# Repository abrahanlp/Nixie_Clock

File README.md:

# Nixie_Clock
 Nixie display clock custom Arduino based.

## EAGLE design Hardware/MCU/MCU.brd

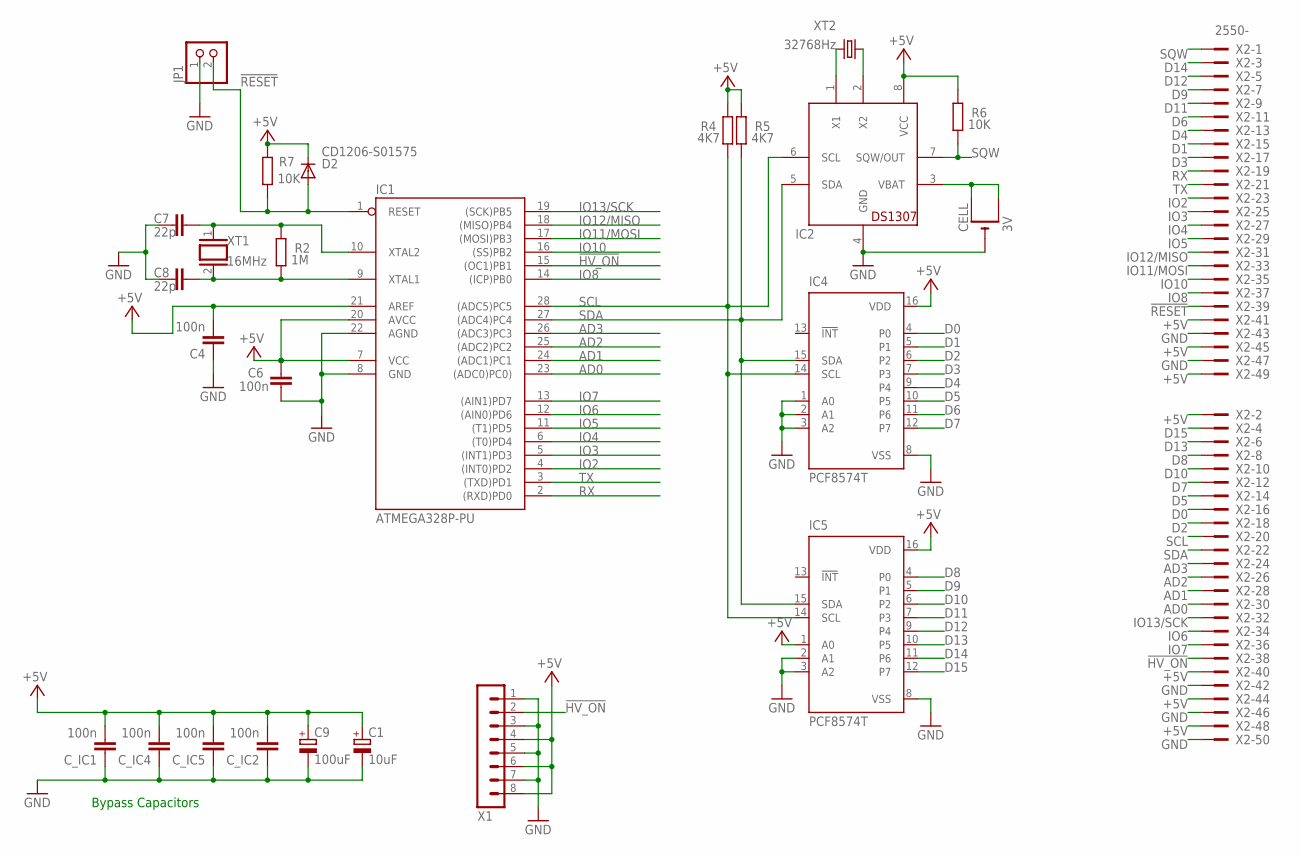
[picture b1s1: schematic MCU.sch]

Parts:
C1: 10uF; 085CS_1AR
C4, C6: 100n; C1206
C7, C8: 22p; C1206
C9: 100uF; E5-10,5
CELL: 3V; CR2032-THRU
C_IC1, C_IC2, C_IC4, C_IC5: 100n; C1206
D2: CD1206-S01575; DO41-10
IC1: ATMEGA328P-PU; DIL28-3
IC2: DS1307; DIL08
IC4, IC5: PCF8574T; SO16W
JP1: PINHD-1X2; 1X02
R2: 1M; M1206
R4, R5: 4K7; M1206
R6, R7: 10K; M1206
X1: MA08-1W
X2: 2550-; PAK100/2500-50
XT1: 16MHz; QS
XT2: 32768Hz; TC26H

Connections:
!HV_ON: IC1.15 ((OC1)PB1), X1.2, X2.38
!RESET: D2.A, IC1.1 (RESET), JP1.2, R7.1, X2.39
+5V: C1.+, C4.2, C6.2, C9.+, C_IC1.2, C_IC2.2, C_IC4.2, C_IC5.2, D2.C, IC1.7 (VCC), IC1.20 (AVCC), IC1.21 (AREF), IC2.8 (VCC), IC4.16 (VDD), IC5.1 (A0), IC5.16 (VDD), R4.2, R5.2, R6.2, R7.2, X1.4, X1.6, X1.8, X2.2, X2.40, X2.41, X2.44, X2.45, X2.48, X2.49
AD0: IC1.23 ((ADC0)PC0)), X2.30
AD1: IC1.24 ((ADC1)PC1), X2.28
AD2: IC1.25 ((ADC2)PC2), X2.26
AD3: IC1.26 ((ADC3)PC3), X2.24
D0: IC4.4 (P0), X2.16
D1: IC4.5 (P1), X2.15
D2: IC4.6 (P2), X2.18
D3: IC4.7 (P3), X2.17
D4: IC4.9 (P4), X2.13
D5: IC4.10 (P5), X2.14
D6: IC4.11 (P6), X2.11
D7: IC4.12 (P7), X2.12
D8: IC5.4 (P0), X2.8
D9: IC5.5 (P1), X2.7
D10: IC5.6 (P2), X2.10
D11: IC5.7 (P3), X2.9
D12: IC5.9 (P4), X2.5
D13: IC5.10 (P5), X2.6
D14: IC5.11 (P6), X2.3
D15: IC5.12 (P7), X2.4
GND: C1.-, C4.1, C6.1, C7.1, C8.1, C9.-, CELL.-, C_IC1.1, C_IC2.1, C_IC4.1, C_IC5.1, IC1.8 (GND), IC1.22 (AGND), IC2.4 (GND), IC4.1 (A0), IC4.2 (A1), IC4.3 (A2), IC4.8 (VSS), IC5.2 (A1), IC5.3 (A2), IC5.8 (VSS), JP1.1, X1.1, X1.3, X1.5, X1.7, X2.42, X2.43, X2.46, X2.47, X2.50
IO2: IC1.4 ((INT0)PD2), X2.23
IO3: IC1.5 ((INT1)PD3), X2.25
IO4: IC1.6 ((T0)PD4), X2.27
IO5: IC1.11 ((T1)PD5), X2.29
IO6: IC1.12 ((AIN0)PD6), X2.34
IO7: IC1.13 ((AIN1)PD7), X2.36
IO8: IC1.14 ((ICP)PB0), X2.37
IO10: IC1.16 ((SS)PB2), X2.35
IO11/MOSI: IC1.17 ((MOSI)PB3), X2.33
IO12/MISO: IC1.18 ((MISO)PB4), X2.31
IO13/SCK: IC1.19 ((SCK)PB5), X2.32
RX: IC1.2 ((RXD)PD0), X2.19
SCL: IC1.28 ((ADC5)PC5), IC2.6 (SCL), IC4.14 (SCL), IC5.14 (SCL), R4.1, X2.20
SDA: IC1.27 ((ADC4)PC4), IC2.5 (SDA), IC4.15 (SDA), IC5.15 (SDA), R5.1, X2.22
SQW: IC2.7 (SQW/OUT), R6.1, X2.1
TX: IC1.3 ((TXD)PD1), X2.21
VBAT: CELL.+1 (+), CELL.+2 (+1), IC2.3 (VBAT)
X1_RTC: IC2.1 (X1), XT2.2
X2_RTC: IC2.2 (X2), XT2.1
XTAL1: C8.2, IC1.9 (XTAL1), R2.1, XT1.2
XTAL2: C7.2, IC1.10 (XTAL2), R2.2, XT1.1

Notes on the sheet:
Bypass Capacitors

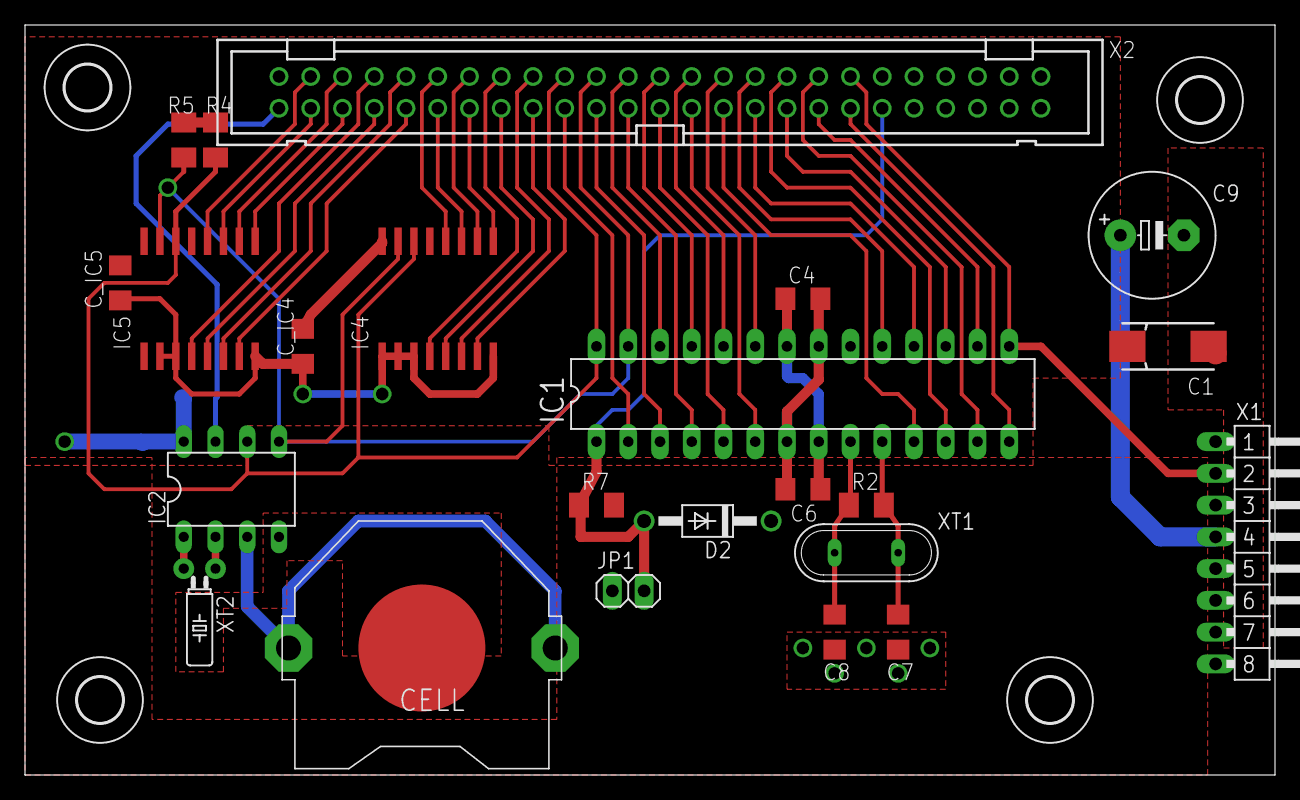
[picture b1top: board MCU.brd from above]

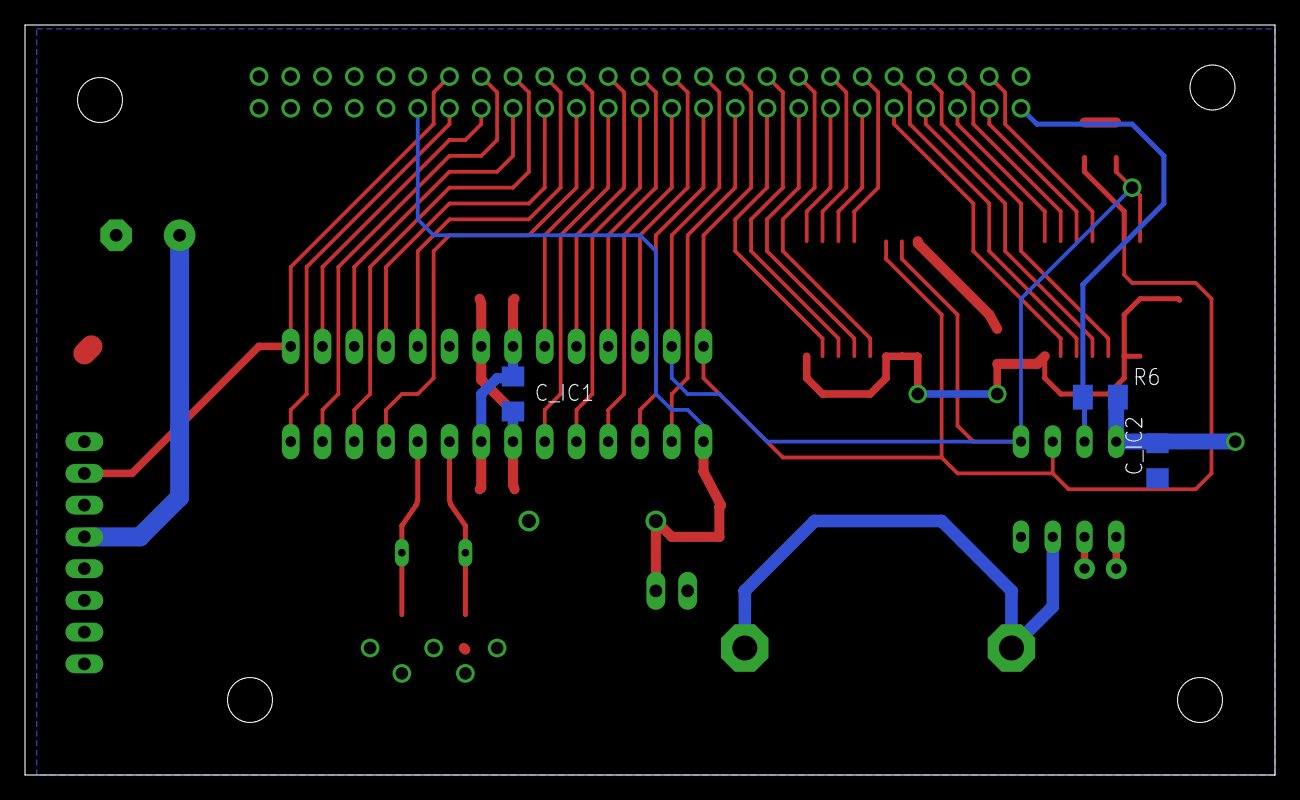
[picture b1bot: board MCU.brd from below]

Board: 2 copper layers, 100.0 x 60.0 mm, 30 parts (3 on the bottom side), 45 nets.

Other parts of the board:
U$1, U$2, U$3, U$4: 3,6

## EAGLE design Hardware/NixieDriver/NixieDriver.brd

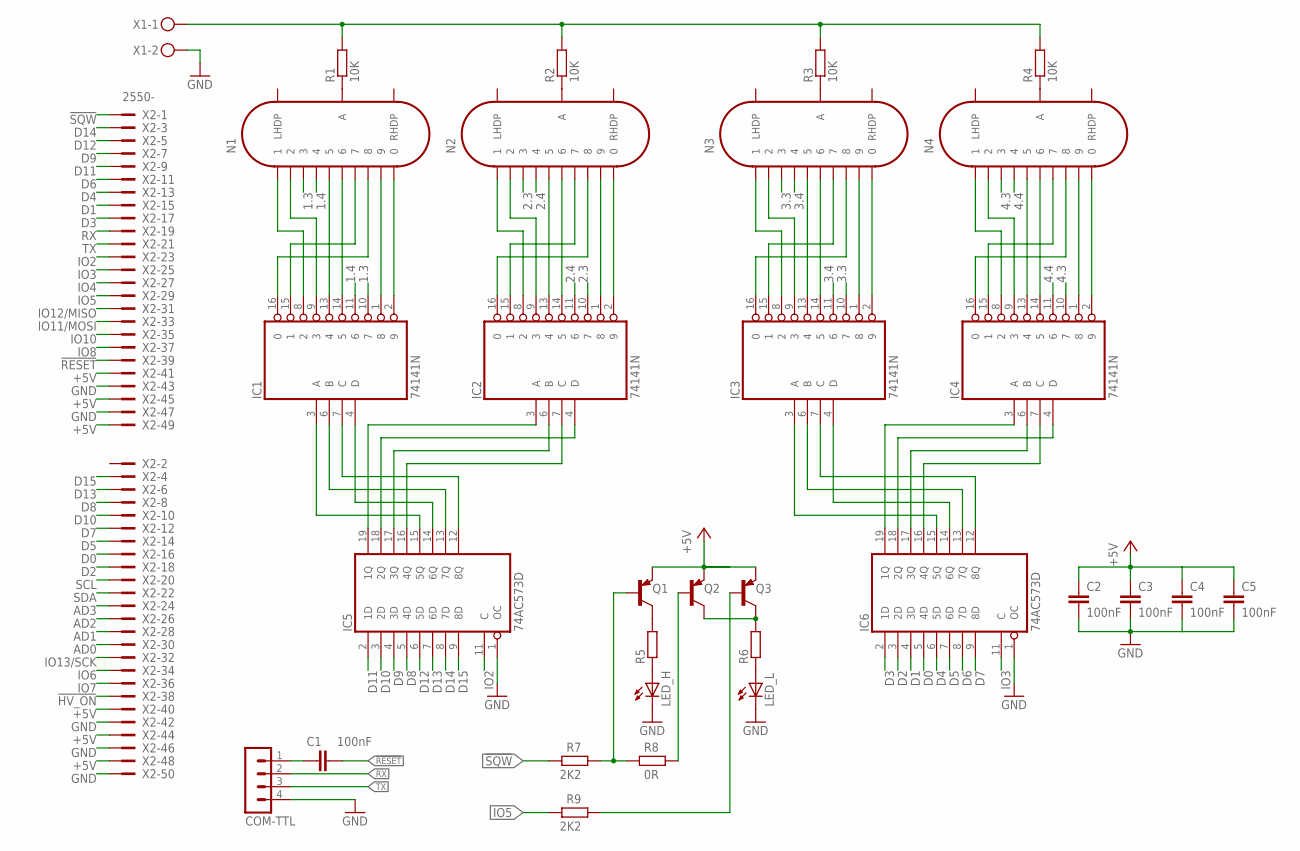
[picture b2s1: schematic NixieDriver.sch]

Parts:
C1, C2, C3, C4, C5: 100nF; C1210
COM-TTL: MA04-1
IC1, IC2, IC3, IC4: 74141N; DIL16
IC5, IC6: 74AC573D; SO20W
LED_H: LED5MM
LED_L: LED5MM
N1, N2, N3, N4: IN-14
Q1, Q2, Q3: BF621-PNP-SOT98-BCE; SOT89-BCE
R1, R2, R3, R4: 10K; 0309V
R5, R6: R-EU_M1206; M1206
R7: 2K2; M1406
R8: 0R; M1406
R9: 2K2; M1206
X1: MKDSN1,5/2-5,08
X2: 2550-; PAK100/2500-50

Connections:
1.0: IC1.2 (9), N1.0
1.1: IC1.8 (2), N1.1
1.2: IC1.9 (3), N1.2
1.3: IC1.10 (7), N1.3
1.4: IC1.11 (6), N1.4
1.5: IC1.13 (4), N1.5
1.6: IC1.14 (5), N1.6
1.7: IC1.15 (1), N1.7
1.8: IC1.16 (0), N1.8
1.9: IC1.1 (8), N1.9
2.0: IC2.2 (9), N2.0
2.1: IC2.8 (2), N2.1
2.2: IC2.9 (3), N2.2
2.3: IC2.10 (7), N2.3
2.4: IC2.11 (6), N2.4
2.5: IC2.13 (4), N2.5
2.6: IC2.14 (5), N2.6
2.7: IC2.15 (1), N2.7
2.8: IC2.16 (0), N2.8
2.9: IC2.1 (8), N2.9
3.0: IC3.2 (9), N3.0
3.1: IC3.8 (2), N3.1
3.2: IC3.9 (3), N3.2
3.3: IC3.10 (7), N3.3
3.4: IC3.11 (6), N3.4
3.5: IC3.13 (4), N3.5
3.6: IC3.14 (5), N3.6
3.7: IC3.15 (1), N3.7
3.8: IC3.16 (0), N3.8
3.9: IC3.1 (8), N3.9
4.0: IC4.2 (9), N4.0
4.1: IC4.8 (2), N4.1
4.2: IC4.9 (3), N4.2
4.3: IC4.10 (7), N4.3
4.4: IC4.11 (6), N4.4
4.5: IC4.13 (4), N4.5
4.6: IC4.14 (5), N4.6
4.7: IC4.15 (1), N4.7
4.8: IC4.16 (0), N4.8
4.9: IC4.1 (8), N4.9
!HV_ON: X2.38
!RESET: C1.2, X2.39
!SQW: R7.2, X2.1
+5V: C2.1, C3.1, C4.1, C5.1, IC1.5 (VCC), IC2.5 (VCC), IC3.5 (VCC), IC4.5 (VCC), IC5.20 (VCC), IC6.20 (VCC), Q1.E, Q2.E, Q3.E, X2.40, X2.41, X2.44, X2.45, X2.48, X2.49
AD0: X2.30
AD1: X2.28
AD2: X2.26
AD3: X2.24
D0: IC6.5 (4D), X2.16
D1: IC6.4 (3D), X2.15
D2: IC6.3 (2D), X2.18
D3: IC6.2 (1D), X2.17
D4: IC6.6 (5D), X2.13
D5: IC6.7 (6D), X2.14
D6: IC6.8 (7D), X2.11
D7: IC6.9 (8D), X2.12
D8: IC5.5 (4D), X2.8
D9: IC5.4 (3D), X2.7
D10: IC5.3 (2D), X2.10
D11: IC5.2 (1D), X2.9
D12: IC5.6 (5D), X2.5
D13: IC5.7 (6D), X2.6
D14: IC5.8 (7D), X2.3
D15: IC5.9 (8D), X2.4
GND: C2.2, C3.2, C4.2, C5.2, COM-TTL.4, IC1.12 (GND), IC2.12 (GND), IC3.12 (GND), IC4.12 (GND), IC5.1 (OC), IC5.10 (GND), IC6.1 (OC), IC6.10 (GND), LED_H.K (C), LED_L.K (C), X1.2, X2.42, X2.43, X2.46, X2.47, X2.50
HIGH_VOLTAGE: R1.2, R2.2, R3.2, R4.2, X1.1
IO2: IC5.11 (C), X2.23
IO3: IC6.11 (C), X2.25
IO4: X2.27
IO5: R9.2, X2.29
IO6: X2.34
IO7: X2.36
IO8: X2.37
IO10: X2.35
IO11/MOSI: X2.33
IO12/MISO: X2.31
IO13/SCK: X2.32
unnamed: IC2.3 (A), IC5.19 (1Q)
unnamed: IC2.4 (D), IC5.18 (2Q)
unnamed: IC2.6 (B), IC5.17 (3Q)
unnamed: IC2.7 (C), IC5.16 (4Q)
unnamed: IC1.3 (A), IC5.15 (5Q)
unnamed: IC1.4 (D), IC5.14 (6Q)
unnamed: IC1.6 (B), IC5.13 (7Q)
unnamed: IC1.7 (C), IC5.12 (8Q)
unnamed: IC4.3 (A), IC6.19 (1Q)
unnamed: IC4.4 (D), IC6.18 (2Q)
unnamed: IC4.6 (B), IC6.17 (3Q)
unnamed: IC4.7 (C), IC6.16 (4Q)
unnamed: IC3.3 (A), IC6.15 (5Q)
unnamed: IC3.4 (D), IC6.14 (6Q)
unnamed: IC3.6 (B), IC6.13 (7Q)
unnamed: IC3.7 (C), IC6.12 (8Q)
unnamed: Q1.C, R5.2
unnamed: LED_H.A, R5.1
unnamed: Q2.C, Q3.C, R6.2
unnamed: LED_L.A, R6.1
unnamed: Q1.B, R7.1, R8.2
unnamed: C1.1, COM-TTL.1
unnamed: Q2.B, R8.1
unnamed: N1.A, R1.1
unnamed: N2.A, R2.1
unnamed: N3.A, R3.1
unnamed: N4.A, R4.1
unnamed: Q3.B, R9.1
RX: COM-TTL.2, X2.19
SCL: X2.20
SDA: X2.22
TX: COM-TTL.3, X2.21

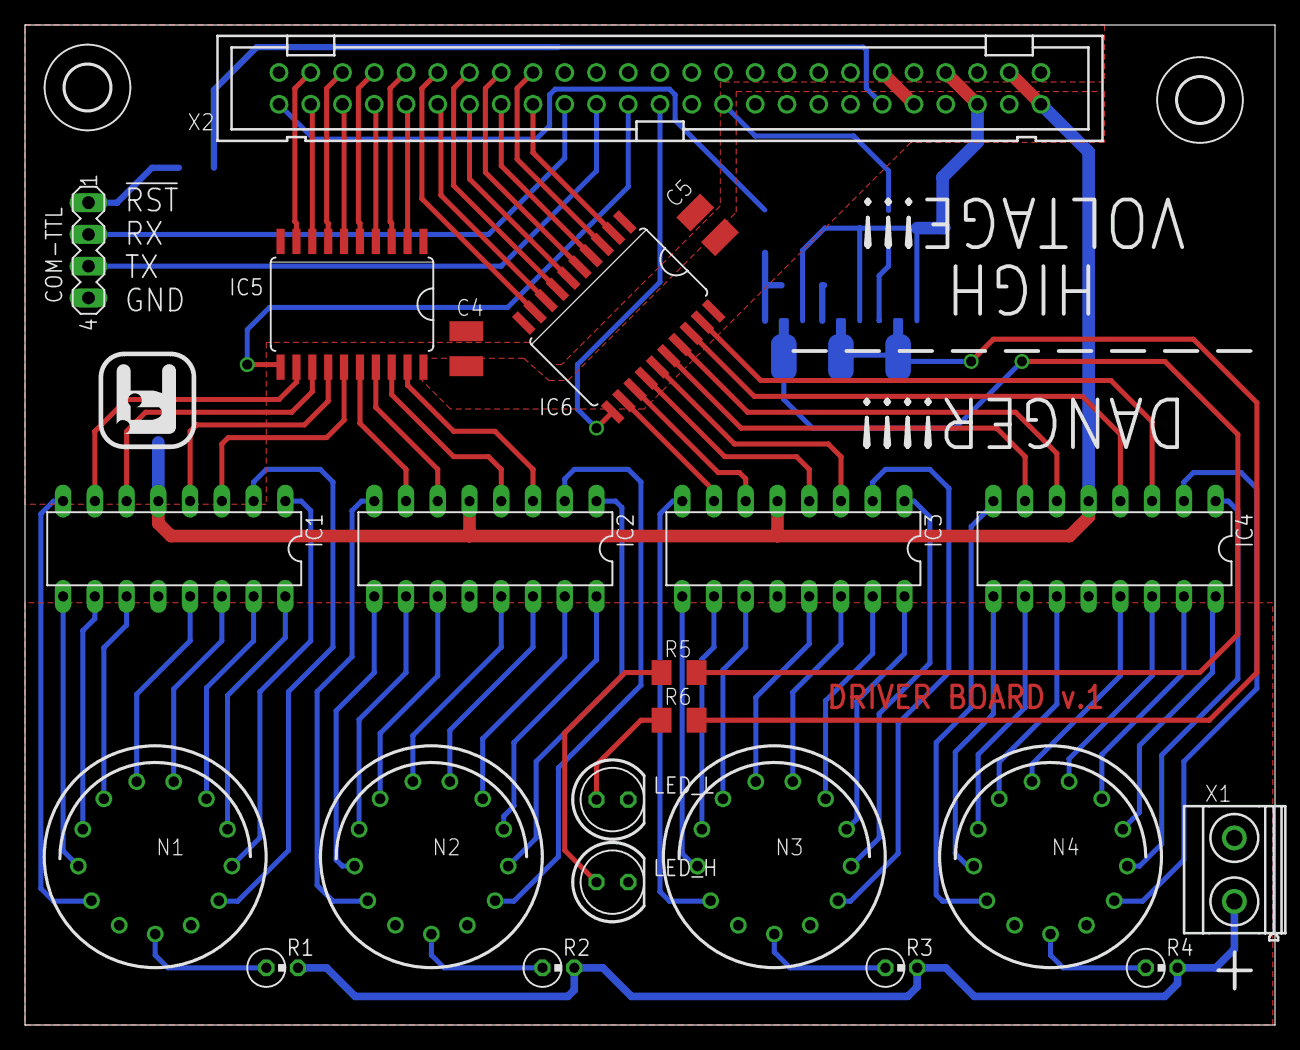
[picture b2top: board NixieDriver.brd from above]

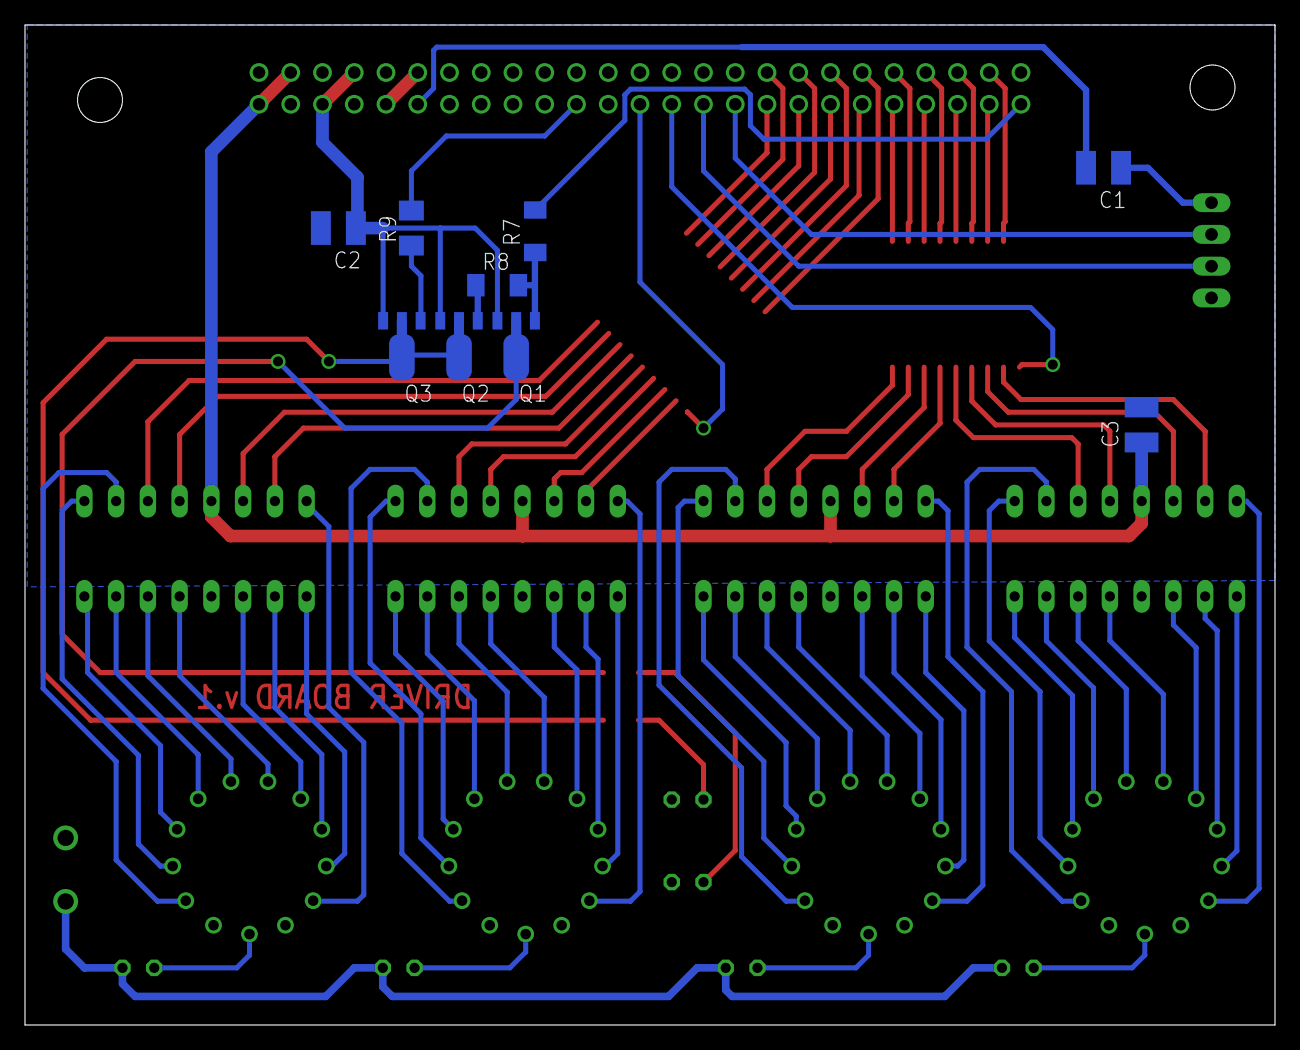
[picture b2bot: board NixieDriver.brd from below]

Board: 2 copper layers, 100.0 x 80.0 mm, 34 parts (9 on the bottom side), 94 nets.

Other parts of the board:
U$1, U$3: 3,6

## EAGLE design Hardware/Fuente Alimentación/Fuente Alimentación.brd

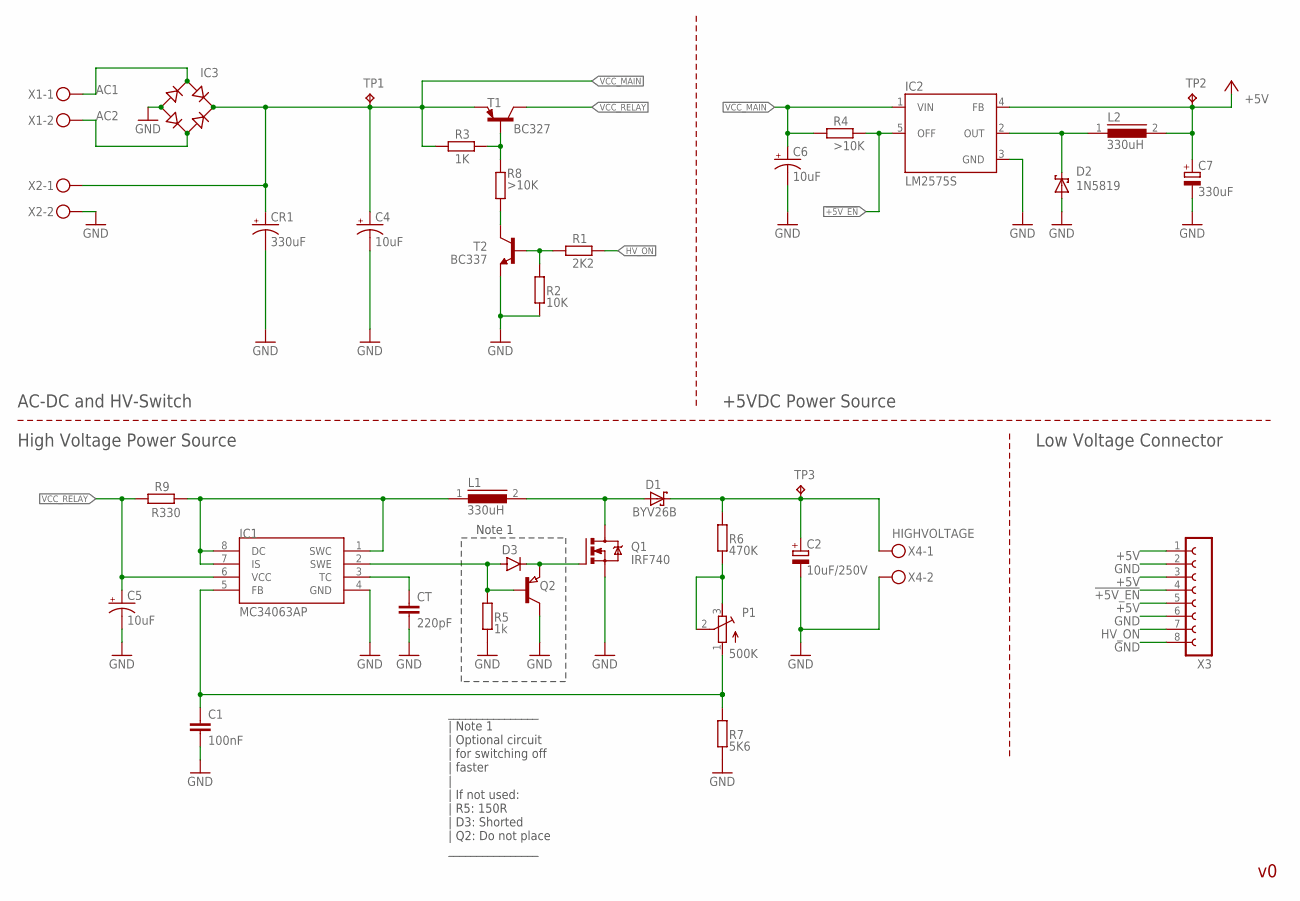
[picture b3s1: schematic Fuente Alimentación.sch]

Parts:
C1: 100nF; C1808
C2: 10uF/250V; E5-13
C4, C5, C6: 10uF; 085CS_1AR
C7: 330uF; E5-10,5
CR1: 330uF; E5-13
CT: 220pF; C025-024X044
D1: BYV26B; DO41-7.6
D2: 1N5819; DO41-7.6
D3: MBR0520LT; SOD123
IC1: MC34063AP; DIL08
IC2: LM2575S; TO263-5
IC3: B-DIL
L1, L2: 330uH; DR125
P1: 500K; RTRIM64W
Q1: IRF740; TO220BV
Q2: PNP-TRANSISTOR_SOT23; SOT23
R1: 2K2; 0207/2V
R2: 10K; 0207/2V
R3: 1K; 0204/5
R4: >10K; 0207/2V
R5: 1k; 0204V
R6: 470K; 0204/7
R7: 5K6; 0204V
R8: >10K; 0204V
R9: R330; 0204V
T1: BC327; TO92
T2: BC337; TO92
TP1, TP2, TP3: TPB1,27; B1,27
X1, X2, X4: MKDSN1,5/2-5,08
X3: FE08W

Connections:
!+5V_EN: IC2.5 (OFF), R4.2, X3.4
+5V: C7.+, IC2.4 (FB), L2.2, TP2.TP, X3.1, X3.3, X3.5
AC1: IC3.AC2, X1.1
AC2: IC3.AC1, X1.2
CT: CT.1, IC1.3 (TC)
GND: C1.2, C2.-, C4.-, C5.-, C6.-, C7.-, CR1.-, CT.2, D2.A, IC1.4 (GND), IC2.3 (GND), IC3.-, Q1.S, Q2.3 (C), R2.1, R5.1, R7.1, T2.1 (E), X2.2, X3.2, X3.6, X3.8, X4.2
HIGHVOLTAGE: C2.+, D1.C, R6.2, TP3.TP, X4.1
HV_ON: R1.2, X3.7
unnamed: D3.C, Q1.G, Q2.2 (E)
unnamed: C1.1, IC1.5 (FB), P1.1 (A), R7.2
unnamed: D2.C, IC2.2 (OUT), L2.1
unnamed: D1.A, L1.2, Q1.D
unnamed: P1.2 (S), P1.3 (E), R6.1
unnamed: IC1.1 (SWC), IC1.7 (IS), IC1.8 (DC), L1.1, R9.2
unnamed: R3.2, R8.2, T1.2 (B)
unnamed: R1.1, R2.2, T2.2 (B)
unnamed: R8.1, T2.3 (C)
SWE: D3.A, IC1.2 (SWE), Q2.1 (B), R5.2
VCC_MAIN: C4.+, C6.+, CR1.+, IC2.1 (VIN), IC3.+, R3.1, R4.1, T1.1 (E), TP1.TP, X2.1
VCC_RELAY: C5.+, IC1.6 (VCC), R9.1, T1.3 (C)

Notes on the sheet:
________________ | Note 1 | Optional circuit | for switching off | faster | | If not used: | R5: 150R | D3: Shorted | Q2: Do not place ________________
Note 1
AC-DC and HV-Switch
+5VDC Power Source
High Voltage Power Source
Low Voltage Connector

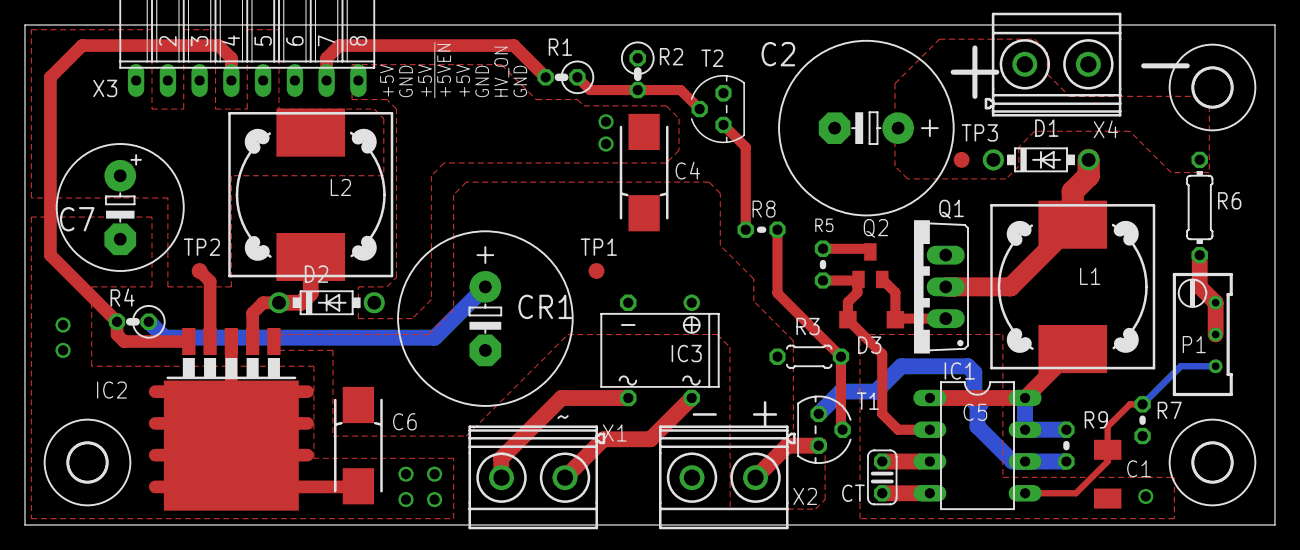
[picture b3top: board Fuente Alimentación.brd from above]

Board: 2 copper layers, 100.0 x 40.0 mm, 40 parts (1 on the bottom side), 20 nets.

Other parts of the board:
U$1, U$2, U$3: 3,0

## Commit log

2024-08-14 Updated schematics.
2024-08-15 Driver board fixes
    Added bypass capacitors.
    Power layout modified.
2024-08-18 RTC basic driver.
2024-08-18 Basic nixie driver, do not work.
2024-08-31 Basic Nixie driver
2024-08-31 Fixed nixie driver schematics, wrong order.
2024-10-12 set_clock() calculate week day. First full integration.
2024-10-12 WDT enabled. Minimal error management.
2024-10-13 Wire is initialized on setup(). RTC functions to manage SQW pin.
2024-10-26 SQW pull-up to VCC, not cell. EMI PCB layout improvements.
2024-10-27 Update time when setting
2025-03-15 Update LICENSE
2025-03-28 Added prototype images
